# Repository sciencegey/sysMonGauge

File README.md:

# sysMonGauge
Fancy System Monitoring Gauge

## Building
The panel is designed to be printed using a standard FDM 3D printer (hence the funky split down the middle), but it would probably be better if you used a laser cutter or CNC router to cut the panel out of plastic or wood.

The rods were machined out of aluminium bar stock, but M8 threaded rod would work just as well.

I build the circuit on perf-board, but PCB files are included.

The dials were printed out onto self-adhesive paper and trimmed around the existing metal dials the gauges came with.

## Parts
<details>

<summary>Parts list</summary>

### Hardware
- 3x 360mm M8 threaded rod
- 12x M8 nuts
- 8x M3 hex-head screw (to attach the panel to the wings)
- 8x M2 hex-head screws and nuts (to attach the 7 segment displays)
- Lots of glue and zip-ties ;)
### Electronics
- 6x 5mA ammeter *"85C1"*
- 1x 5 position rotary switch *"LW26"*
- 2x 0.36" 4-digit 7 segment display *"TM1637"*
- 1M 144 LED WS2812B LED strip
- 6x 1k variable resistor
- 1x Raspberry Pi Pico
##
- 1x 330uF 16V electrolytic capacitor
- 5x 3mm red LED with holder
- 6x JST XH 1x2 connector
- 1x JST XH 1x5 connector
- 2x JST XH 1x4 connector
- 1x JST XH 1x6 connector
- 1x 2N7000 (TO-92)
- 2x 10k resistor
- 2x 470k resistor
</details>

## Installation
Open a command prompt as administrator and run `install.bat` to install the server as a Windows service, make sure the panel is plugged in, and it should spring to life!

Alternatively, to run the server standalone, make sure the service is stopped (`python sysMonSender.py stop`), then run `python sysMonSender.py debug` as an administrator.

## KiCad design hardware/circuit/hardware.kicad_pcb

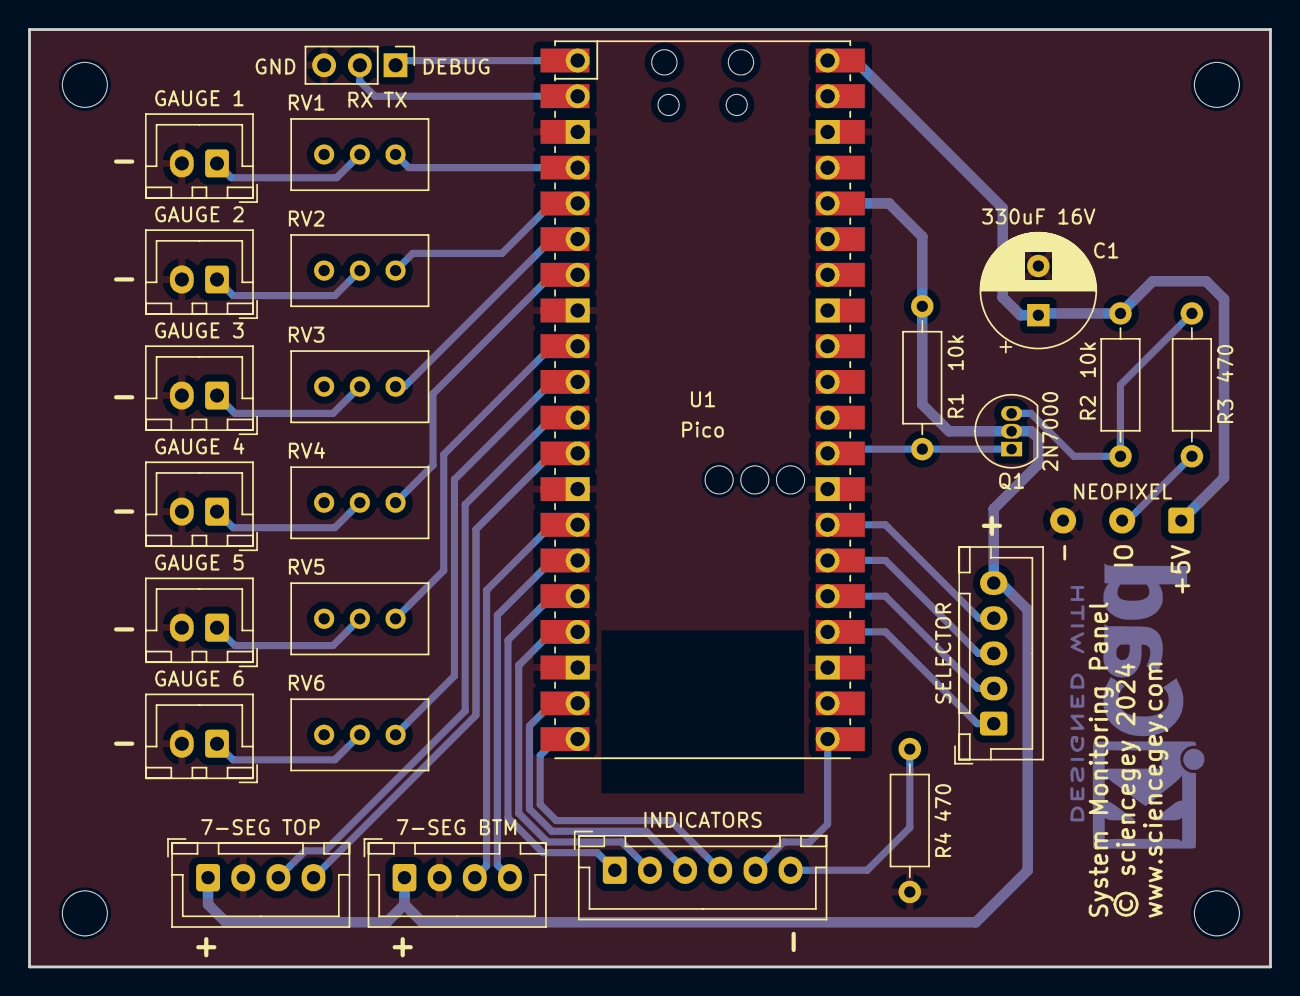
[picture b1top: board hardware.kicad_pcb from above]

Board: 2 copper layers, 88.3 x 66.7 mm, 25 parts (0 on the bottom side), 34 nets.

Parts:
C1: 330uF 16V; CP_Radial_D8.0mm_P3.50mm
J1: GAUGE 1; JST_XH_B2B-XH-A_1x02_P2.50mm_Vertical
J2: DEBUG; PinHeader_1x03_P2.54mm_Vertical
J3: GAUGE 2; JST_XH_B2B-XH-A_1x02_P2.50mm_Vertical
J4: GAUGE 3; JST_XH_B2B-XH-A_1x02_P2.50mm_Vertical
J5: NEOPIXEL; SolderWire-0.25sqmm_1x03_P4.2mm_D0.65mm_OD1.7mm
J6: GAUGE 4; JST_XH_B2B-XH-A_1x02_P2.50mm_Vertical
J7: GAUGE 5; JST_XH_B2B-XH-A_1x02_P2.50mm_Vertical
J8: SELECTOR; JST_XH_B5B-XH-A_1x05_P2.50mm_Vertical
J9: GAUGE 6; JST_XH_B2B-XH-A_1x02_P2.50mm_Vertical
J10: 7-SEG TOP; JST_XH_B4B-XH-A_1x04_P2.50mm_Vertical
J11: 7-SEG BTM; JST_XH_B4B-XH-A_1x04_P2.50mm_Vertical
J12: INDICATORS; JST_XH_B6B-XH-A_1x06_P2.50mm_Vertical
Q1: 2N7000; TO-92_Inline
R1, R2: 10k; R_Axial_DIN0207_L6.3mm_D2.5mm_P10.16mm_Horizontal
R3, R4: 470; R_Axial_DIN0207_L6.3mm_D2.5mm_P10.16mm_Horizontal
RV1, RV2, RV3, RV4, RV5, RV6: 1K; Potentiometer_Bourns_3296W_Vertical
U1: Pico; RPi_Pico_W_SMD_TH

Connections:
+3.3V: J8.5, J10.1, J11.1, Q1.2 (G), R1.1, U1.36 (3V3)
+5V: C1.1, J5.1, R2.1, U1.40 (VBUS)
/LED0_CLK: J10.3, U1.11 (GPIO8)
/LED0_DIO: J10.4, U1.12 (GPIO9)
/LED1_CLK: J11.3, U1.14 (GPIO10)
/LED1_DIO: J11.4, U1.15 (GPIO11)
/RX: J2.2, U1.2 (GPIO1)
/TX: J2.1, U1.1 (GPIO0)
Earth: C1.2, J1.2, J2.3, J3.2, J4.2, J5.3, J6.2, J7.2, J9.2, J10.2, J11.2, R4.2, U1.3 (GND), U1.8 (GND), U1.13 (GND), U1.18 (GND), U1.23 (GND), U1.28 (GND), U1.38 (GND)
unnamed: J1.1, RV1.2
unnamed: J3.1, RV2.2
unnamed: J4.1, RV3.2
unnamed: J5.2, R3.2
unnamed: J6.1, RV4.2
unnamed: J7.1, RV5.2
unnamed: J8.1, U1.24 (GPIO18)
unnamed: J8.2, U1.25 (GPIO19)
unnamed: J8.3, U1.26 (GPIO20)
unnamed: J8.4, U1.27 (GPIO21)
unnamed: J9.1, RV6.2
unnamed: J12.1, U1.16 (GPIO12)
unnamed: J12.2, U1.17 (GPIO13)
unnamed: J12.3, U1.19 (GPIO14)
unnamed: J12.4, U1.20 (GPIO15)
unnamed: J12.5, U1.21 (GPIO16)
unnamed: J12.6, R4.1
unnamed: Q1.3 (D), R2.2, R3.1
unnamed: Q1.1 (S), R1.2, U1.29 (GPIO22)
unnamed: RV1.1, U1.4 (GPIO2)
unnamed: RV2.1, U1.5 (GPIO3)
unnamed: RV3.1, U1.6 (GPIO4)
unnamed: RV4.1, U1.7 (GPIO5)
unnamed: RV5.1, U1.9 (GPIO6)
unnamed: RV6.1, U1.10 (GPIO7)

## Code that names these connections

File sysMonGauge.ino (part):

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#define networkRecvPin 7

// Pins for the 7 segment displays
#define LED0_CLK 8
#define LED0_DIO 9
#define LED1_CLK 10
#define LED1_DIO 11

// Pins used for the rotary switch
const uint8_t swPins[] = {18, 19, 20, 21};
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

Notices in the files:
hardware/circuit/hardware.kicad_pcb:
©️ sciencegey 2024
